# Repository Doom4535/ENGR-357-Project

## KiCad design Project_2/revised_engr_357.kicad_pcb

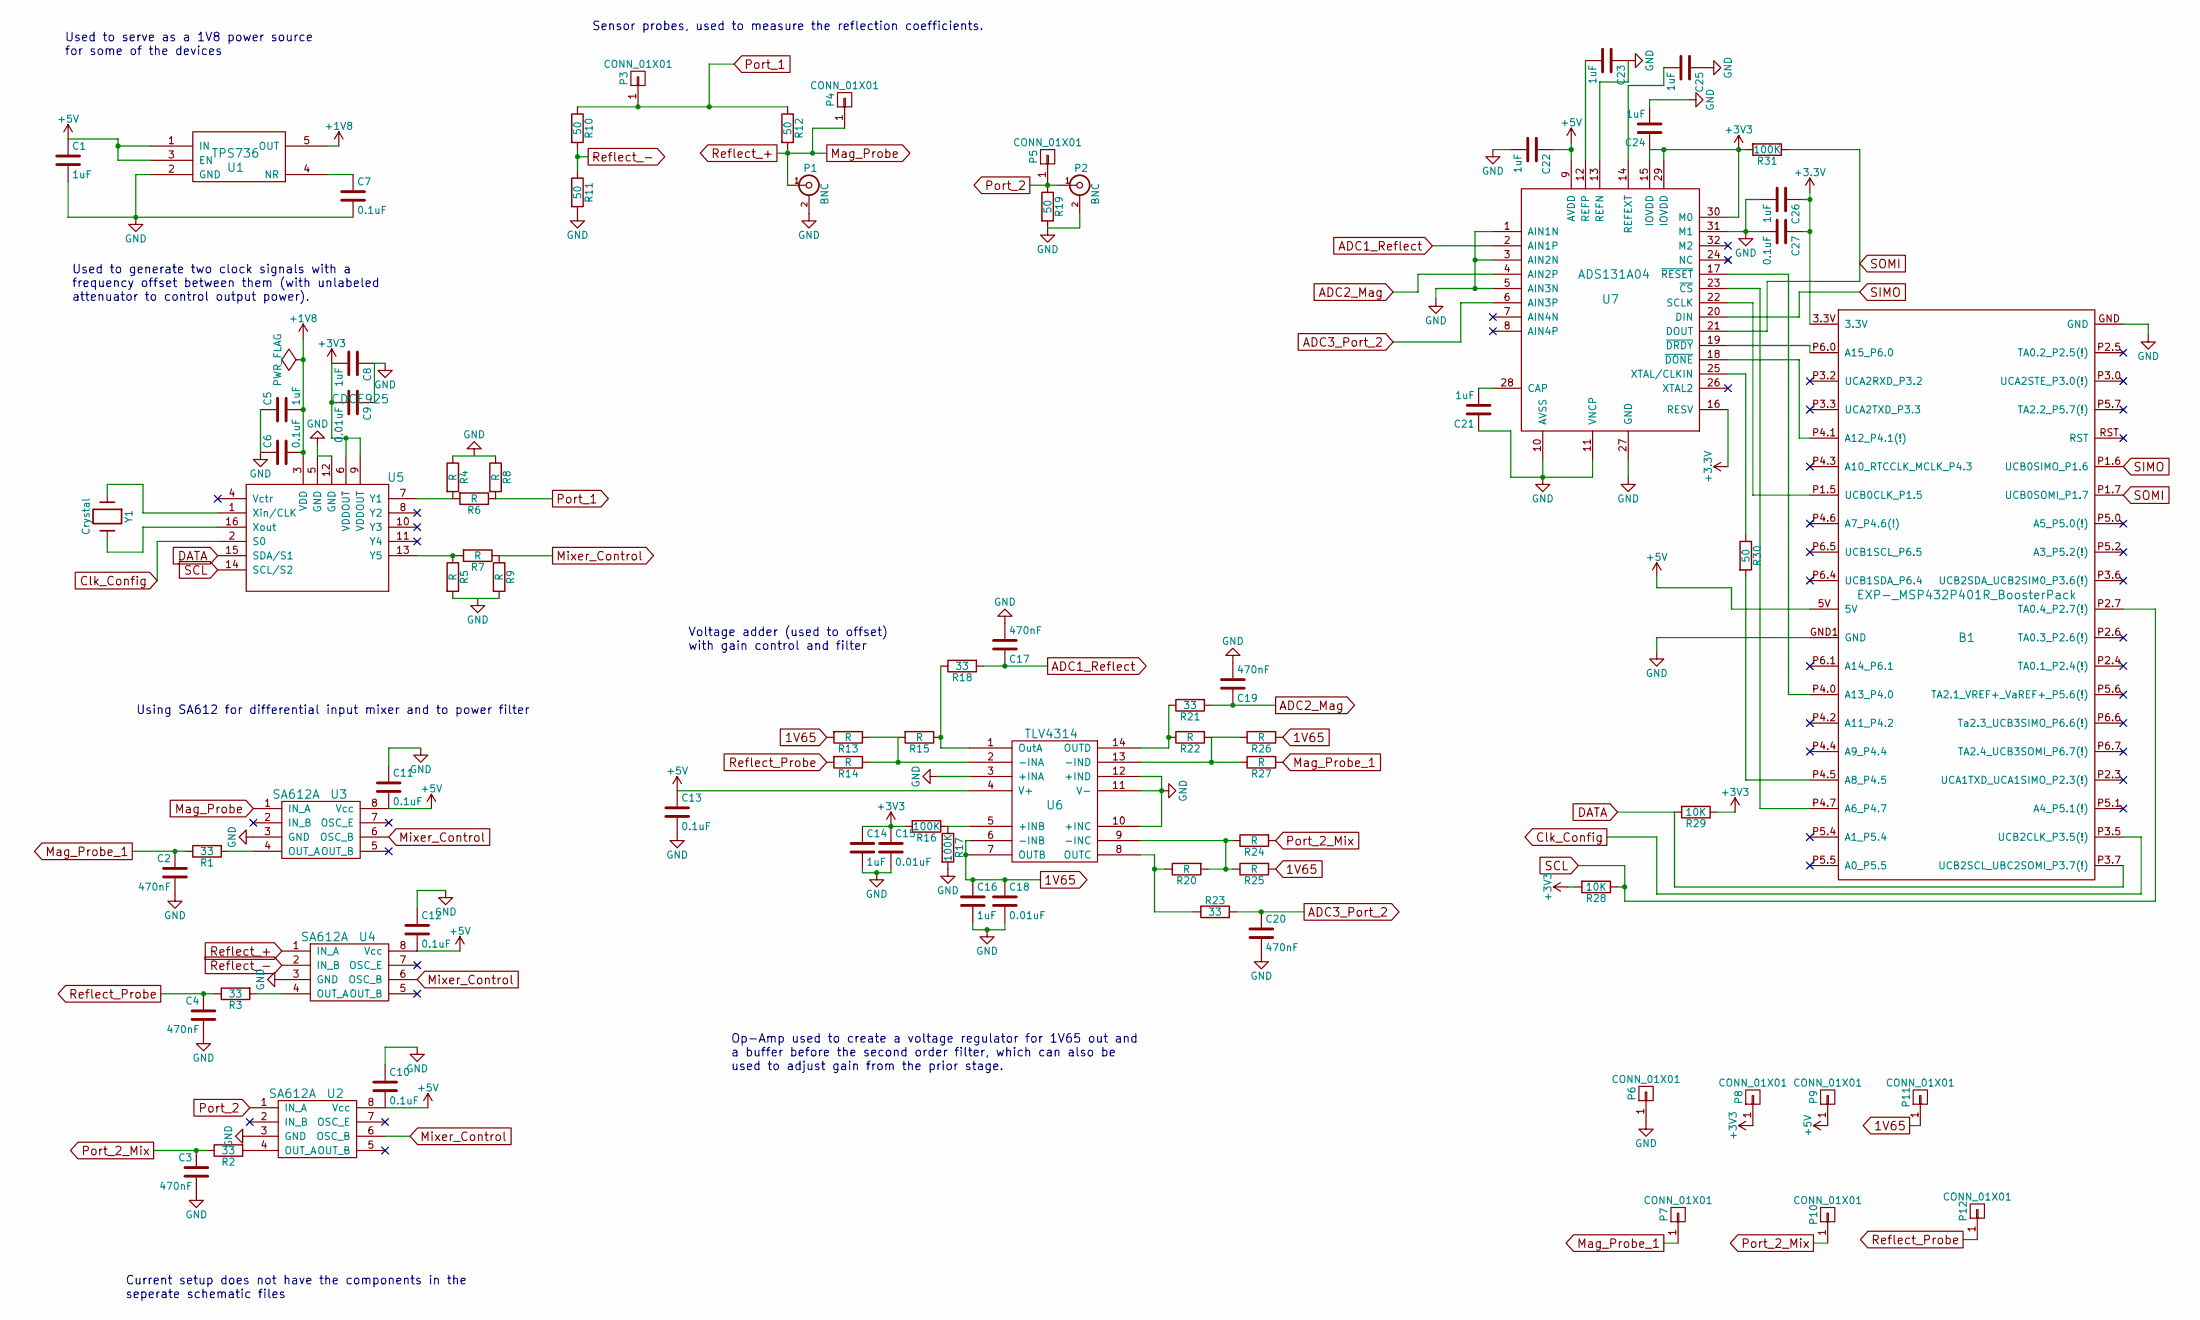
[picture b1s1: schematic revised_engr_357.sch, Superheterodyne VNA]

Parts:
B1: EXP-_MSP432P401R_BoosterPack; TI_BoosterPack
C1, C5, C8, C14, C16, C21, C22, C23, C24, C25, C26: 1uF; C_0805
C2, C3, C4, C17, C19, C20: 470nF; C_0805
C6, C7, C10, C11, C12, C13, C27: 0.1uF; C_0805
C9, C15, C18: 0.01uF; C_0805
P1, P2: BNC; BNC_Socket_TYCO-AMP
P3, P4, P5, P6, P7, P8, P9, P10, P11, P12: CONN_01X01; Measurement_Point_Round-SMD-Pad_Small
R1, R2, R3, R18, R21, R23: 33; R_0805
R4, R5, R6, R7, R8, R9, R13, R14, R15, R20, R22, R24, R25, R26, R27: R; R_0805
R10, R11, R12, R19, R30: 50; R_0805
R16, R17, R31: 100K; R_0805
R28, R29: 10K; R_0805
U1: TPS736; SOT-23-5
U2, U3, U4: SA612A; SO-8
U5: CDCE925; TSSOP-16_4.4x5mm_Pitch0.65mm
U6: TLV4314; TSSOP-14_4.4x5mm_Pitch0.65mm
U7: ADS131A04; LQFP-32_5x5mm_Pitch0.5mm
Y1: Crystal; Crystal_SMD_2520_4Pads

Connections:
1V65: C16.1, C18.1, P11.1, R13.2, R25.2, R26.2, U6.6 (-INB), U6.7 (OUTB)
+1V8: C5.2, C6.2, U1.5 (OUT), U5.3 (VDD)
+5V: B1.5V, C1.1, C10.2, C11.2, C12.2, C13.1, C22.1, P9.1, U1.1 (IN), U1.3 (EN), U2.8 (Vcc), U3.8 (Vcc), U4.8 (Vcc), U6.4 (V+), U7.9 (AVDD)
ADC1_Reflect: C17.1, R18.2, U7.2 (AIN1P)
ADC2_Mag: C19.1, R21.2, U7.4 (AIN2P)
ADC3_Port_2: C20.1, R23.2, U7.6 (AIN3P)
Clk_Config: B1.P3.5 (UCB2CLK_P3.5(!)), U5.2 (S0)
DATA: B1.P3.7 (UCB2SCL_UBC2SOMI_P3.7(!)), R29.2, U5.15 (SDA/S1)
Mag_Probe: P1.1 (In), P4.1, R12.2, U3.1 (IN_A), U4.1 (IN_A)
Mag_Probe_1: C2.1, P7.1, R1.1, R27.2
Mixer_Control: R7.1, R9.1, U2.6 (OSC_B), U3.6 (OSC_B), U4.6 (OSC_B)
unnamed: B1.P1.5 (UCB0CLK_P1.5), U7.22 (SCLK)
unnamed: B1.P4.0 (A13_P4.0), U7.17 (~RESET)
unnamed: B1.P4.1 (A12_P4.1(!)), U7.18 (~DONE)
unnamed: B1.P4.5 (A8_P4.5), R30.2
unnamed: B1.P4.7 (A6_P4.7), U7.23 (~CS)
unnamed: B1.P6.0 (A15_P6.0), U7.19 (~DRDY)
unnamed: C7.1, U1.4 (NR)
unnamed: C21.2, U7.28 (CAP)
unnamed: C23.2, U7.12 (REFP)
unnamed: C25.2, U7.14 (REFEXT)
unnamed: R1.2, U3.4 (OUT_A)
unnamed: R2.2, U2.4 (OUT_A)
unnamed: R3.2, U4.4 (OUT_A)
unnamed: R4.2, R6.2, U5.7 (Y1)
unnamed: R5.1, R7.2, U5.13 (Y5)
unnamed: R13.1, R14.1, R15.2, U6.2 (-INA)
unnamed: R15.1, R18.1, U6.1 (OutA)
unnamed: R16.1, R17.1, U6.5 (+INB)
unnamed: R20.1, R23.1, U6.8 (OUTC)
unnamed: R20.2, R24.1, R25.1, U6.9 (-INC)
unnamed: R21.1, R22.1, U6.14 (OUTD)
unnamed: R22.2, R26.1, R27.1, U6.13 (-IND)
unnamed: R30.1, U7.25 (XTAL/CLKIN)
unnamed: U5.1 (Xin/CLK), Y1.1
unnamed: U5.16 (Xout), Y1.2
Port_1: P3.1, R6.1, R8.2, R10.1, R12.1
Port_2: P2.1 (In), P5.1, R19.1, U2.1 (IN_A)
Port_2_Mix: C3.1, P10.1, R2.1, R24.2
Reflect_-: R10.2, R11.1, U4.2 (IN_B)
Reflect_Probe: C4.1, P12.1, R3.1, R14.2
SCL: B1.P2.7 (TA0.4_P2.7(!)), R28.1, U5.14 (SCL/S2)
SIMO: B1.P1.6 (UCB0SIMO_P1.6), U7.20 (DIN)
SOMI: B1.P1.7 (UCB0SOMI_P1.7), R31.1, U7.21 (DOUT)

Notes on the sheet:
Op-Amp used to create a voltage regulator for 1V65 out and a buffer before the second order filter, which can also be used to adjust gain from the prior stage.
Using SA612 for differential input mixer and to power filter
Used to generate two clock signals with a frequency offset between them (with unlabeled attenuator to control output power).
Used to serve as a 1V8 power source for some of the devices
Sensor probes, used to measure the reflection coefficients.
Current setup does not have the components in the seperate schematic files
Voltage adder (used to offset) with gain control and filter

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
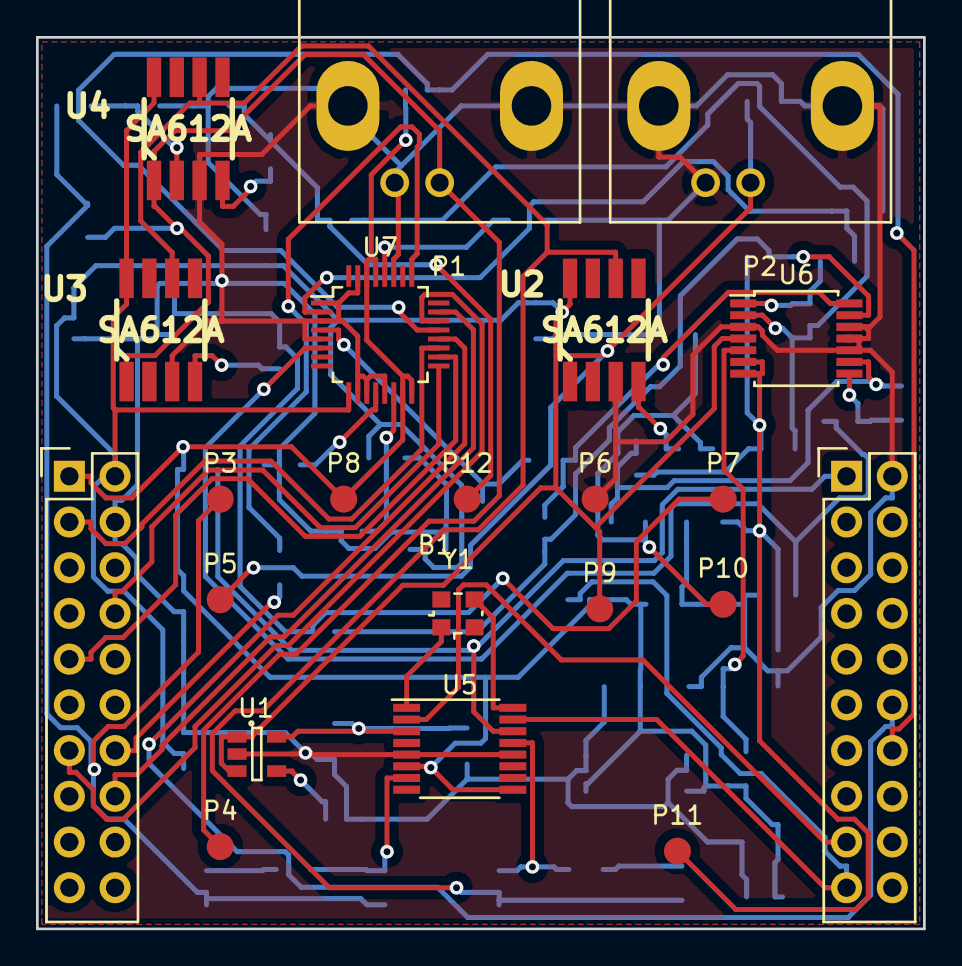
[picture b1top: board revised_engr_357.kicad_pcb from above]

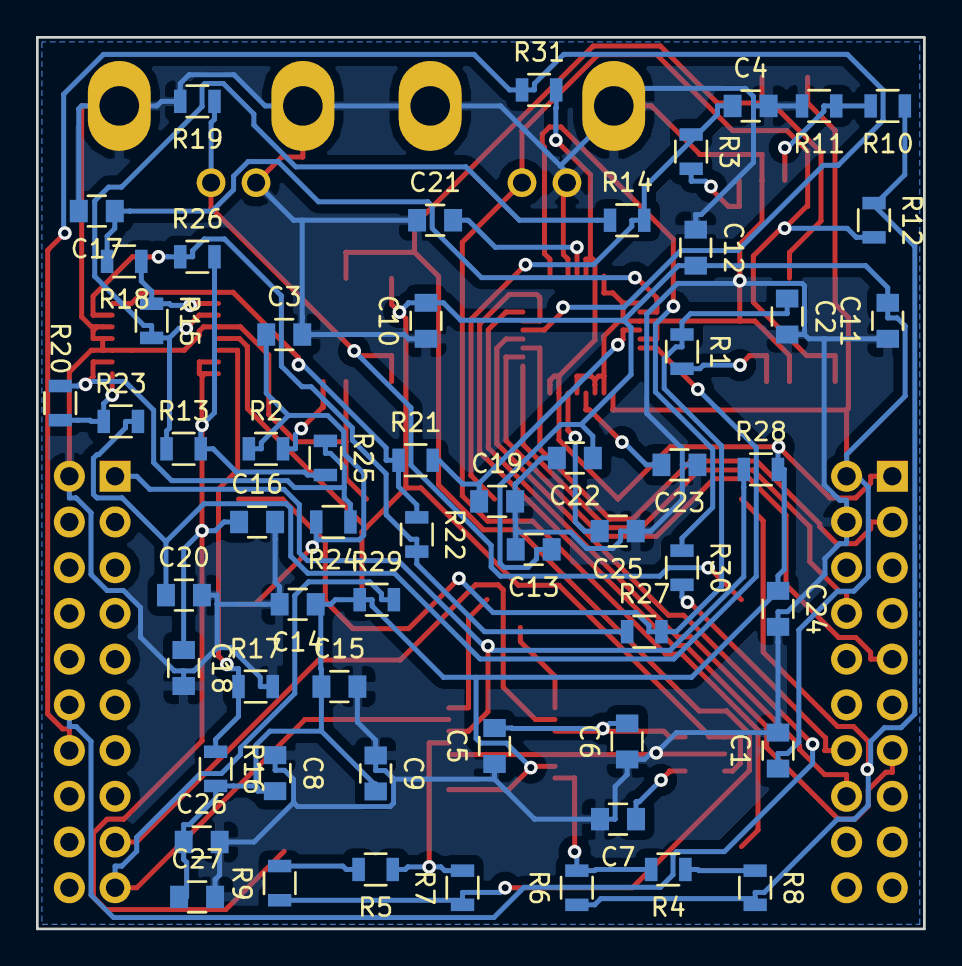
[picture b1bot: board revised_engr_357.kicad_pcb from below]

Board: 2 copper layers, 49.3 x 49.5 mm, 79 parts (58 on the bottom side), 48 nets.

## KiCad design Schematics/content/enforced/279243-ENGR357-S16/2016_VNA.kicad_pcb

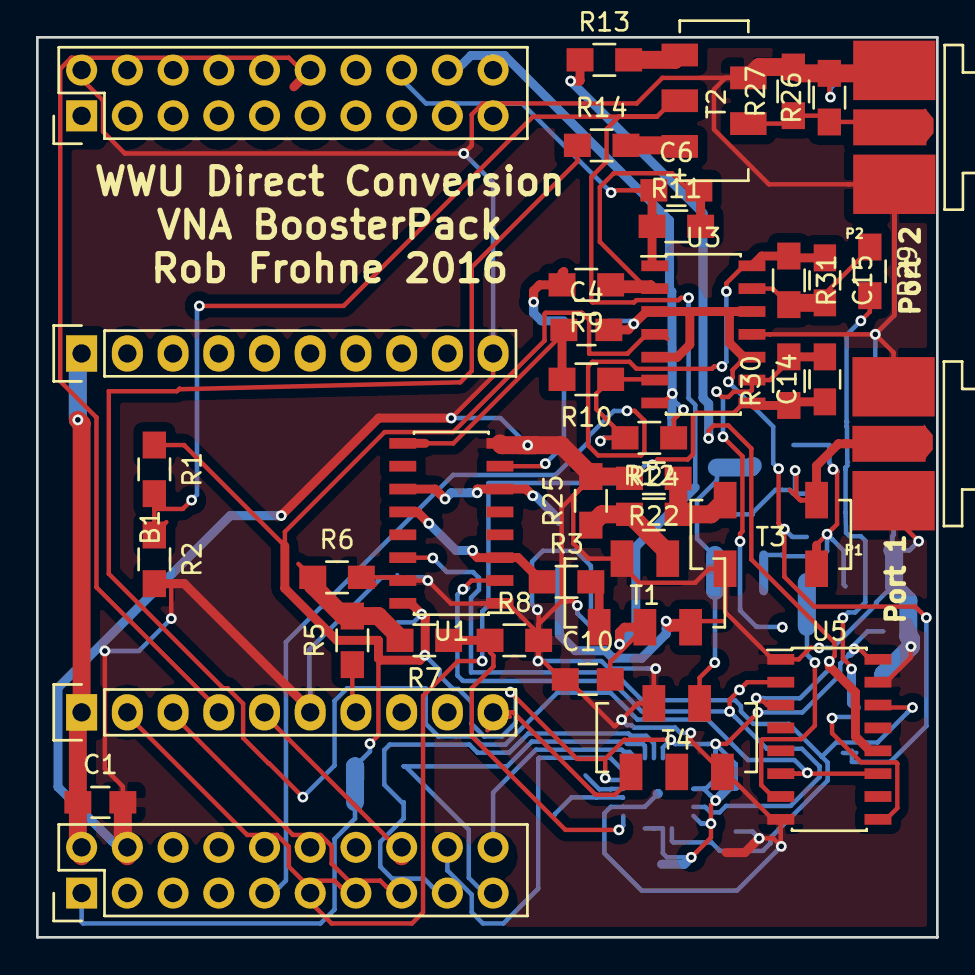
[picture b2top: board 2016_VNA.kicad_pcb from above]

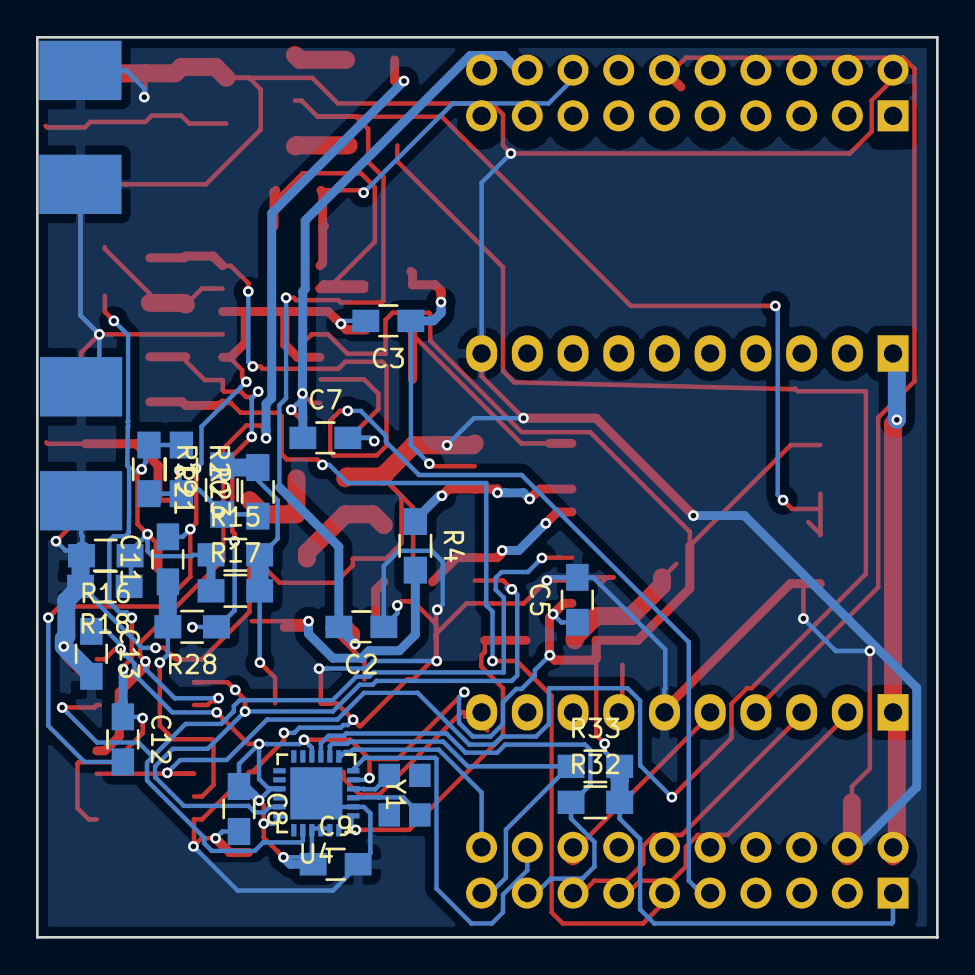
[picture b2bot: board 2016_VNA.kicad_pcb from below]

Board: 2 copper layers, 50.0 x 50.0 mm, 61 parts (23 on the bottom side), 47 nets.

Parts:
B1: EXP-_MSP432P401R_BoosterPack; TI_BoosterPack
C1, C2, C3, C4, C10, C11, C12: 0.1uF; C_0805_HandSoldering
C5, C13: 1.0uF; C_0805_HandSoldering
C6: 0.01 uF; C_0805_HandSoldering
C7, C14, C15: 0.01uF; C_0805_HandSoldering
C8, C9: 1.0 uF; C_0805_HandSoldering
P1, P2: BNC; SMA_EDGE
R1, R2: 2.2K; R_0805_HandSoldering
R3, R4, R13, R14: 1; R_0805_HandSoldering
R5, R7: 51; R_0805_HandSoldering
R6: 120; R_0805_HandSoldering
R8: 36; R_0805_HandSoldering
R9, R22, R24, R25, R28: R; R_0805_HandSoldering
R10, R29: 10; R_0805_HandSoldering
R11, R12, R30, R31: 4.7K; R_0805_HandSoldering
R15, R16, R17, R18, R19, R20, R21, R23, R26, R27: 100; R_0805_HandSoldering
R32, R33: 10K; R_0805_HandSoldering
T1, T2: 50:200 ohm; 4_to_1_Transmission_Line_Transformer
T3: Balun; 1_to_1_Balun
T4: 4:1 (Z); 4_to_1_Transmission_Line_Transformer
U1, U5: TS3A5017; SOIC-16_3.9x9.9mm_Pitch1.27mm
U2: HC-SR08_DDS_Module
U3: LMV324; SOIC-14_3.9x8.7mm_Pitch1.27mm
U4: 5P49V5923; NLG24_4x4mm_Pitch0.5mm
Y1: Xtal; JA4

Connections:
1.65: C3.2, C4.2, C11.2, C12.2, U3.3, U3.5, U3.10, U3.12
1.65V: C2.2, C10.2, R1.2, R2.1, T1.2, T2.2
4XF_I: U1.14, U4.20, U5.14
4XF_Q: U1.2, U4.17, U5.2
+3V3: B1.3.3V, C5.1, C8.1, C9.1, C13.1, R1.1, R32.2, R33.2, U1.16, U3.4, U4.5, U4.10, U4.15, U4.18, U4.21, U4.22, U4.23, U5.16
+5V: B1.5V, C1.1, U2.J2-1, U2.J4-1
CKSEL: B1.P5.4, U4.6
DDS_RST: B1.P4.7, U2.J4-5
FQ_UD: B1.P4.6, U2.J4-3
F_SINE: T4.3, U2.J410
GND: B1.GND, B1.GND1, C1.2, C2.1, C5.2, C8.2, C9.2, C10.1, C13.2, P1.2, P2.2, R2.2, R6.2, R8.2, R16.2, R18.2, R22.2, R25.2, R26.2, R27.2, T1.5, T2.5, T3.3, T4.1, T4.5, U1.1, U1.8, U1.15, U2.J4-6, U2.J210, U3.11, U4.2, U4.EPAD, U5.1, U5.8, U5.15
MO: B1.P1.6, U2.J4-4
unnamed: C3.1, R9.2, U1.7
unnamed: C4.1, R10.2, U1.9
unnamed: C6.2, R9.1, R11.2, U3.2
unnamed: C7.2, R10.1, R12.2, U3.6
unnamed: C11.1, R28.2, U5.7
unnamed: C12.1, R29.2, U5.9
unnamed: C14.2, R28.1, R30.2, U3.9
unnamed: C15.2, R29.1, R31.2, U3.13
unnamed: P1.1, R19.2, R20.2, R21.1, R23.1, T3.2
unnamed: R3.1, U1.3, U1.12
unnamed: R3.2, T1.3
unnamed: R4.1, U1.6, U1.11
unnamed: R4.2, T1.1
unnamed: R5.1, U2.J4-7
unnamed: R5.2, R6.1, R7.2
unnamed: R7.1, R8.1, U4.1
unnamed: R13.1, U5.3, U5.12
unnamed: R13.2, T2.3
unnamed: R14.1, U5.6, U5.11
unnamed: R14.2, T2.1
unnamed: R15.1, R16.1, R17.1, R18.1, R19.1, R20.1, T3.1
unnamed: R15.2, R17.2, R21.2, R23.2, T4.4
unnamed: R22.1, R24.2, T3.4
unnamed: U4.3, Y1.1
unnamed: U4.4, Y1.2
S11: R24.1, R25.1, T1.4
S11_I: B1.P5.0, C6.1, R11.1, U3.1
S11_Q: B1.P5.2, C7.1, R12.1, U3.7
S21: P2.1, R26.1, R27.1, T2.4
S21_I: B1.P4.3, C14.1, R30.1, U3.8
S21_Q: B1.P4.1, C15.1, R31.1, U3.14
SCL: B1.P6.5, R32.1, U4.9
SCLK: B1.P1.5, U2.J4-2
SD: B1.P5.5, U4.7
SDA: B1.P6.4, R33.1, U4.8

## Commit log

2016-04-19 Updating to fix broken diagrams
2016-04-19 Adding .gitignore
2016-04-20 Adding in additional library for the crystal that may be used and adding in some additional connections.
2016-04-20 Adding in some extra files and diagrams
2016-04-20 Adding in header pins for the MSP432 to a seperate library and moving some wiring
2016-04-20 Adding in simple voltage divider till a regulator can be decided on (preferably from TI), also added some power connections
2016-04-22 Adding in class libraries, extract the MSP432 library and change to using it instead of the current one
2016-04-22 Updated master by merging developement into it
2016-04-22 This closes #2 and adds a few wires
2016-04-25 Fixing flipped pins on the ADC
2016-04-25 added voltage regulator
2016-04-26 Updating, starting probes
2016-04-26 adding in bypass capacitors
2016-04-26 adding more component values
2016-04-26 saving before converting probes to work with reflection coefficient
2016-04-26 converted first probe to use reflection coefficient
2016-04-26 updated to use s-parameters (reflection coefficients) still uses only a first order low-pass filter (need to update to a second order)
2016-04-26 adding in export files
2016-04-27 Adding in two pullup resistors and the 3rd probe, also attached several datasheets
2016-04-28 probe fixed
2016-04-28 adding in export and renamed a flag
2016-04-28 Adding in second version of project with better organized schematic
2016-04-28 moving some folders around and performing minor housekeeping
2016-04-29 Finishing v2 of the schematic
2016-04-29 adding in pull up resistors
2016-04-29 adding in additional pdf
2016-04-29 added in resistor on clock source to ADC
2016-04-29 updating libraries to relative paths
2016-04-30 updating design, fixed low-pass filters, ect
2016-05-01 adding archive and pdf
2016-05-01 fixing voltage offset of transformer and adding in a 1V65 source
2016-05-02 adding in AVdd reference to the differential amps
2016-05-02 deleted random ground off page
2016-05-02 cleaning up schematic layout
2016-05-02 cleaning up some of the layouts and improved voltage regulator
2016-05-04 updating schematic to use new mixer
2016-05-04 adding in mixer library
2016-05-04 updating pdf
2016-05-04 finishing new mixers
2016-05-06 partial fix
2016-05-08 fixed probes, removed third order filter, fixed electrical rules checks
2016-05-08 working towards pcb
2016-05-08 working on adding footprints
2016-05-08 starting pcb layout
2016-05-08 fixed some errors and still working on pcb
2016-05-08 working on pcb layout
2016-05-08 testing different pcb layouts
2016-05-09 modifying files
2016-05-09 redoing pcb
2016-05-09 uploading pcb without ground plane
2016-05-09 finished preliminary schematic and pcb
2016-05-09 changning via size and adding test points
2016-05-09 adding in the ground pours that were forgotten in the previous commit
2016-05-09 adding in missing footprint library
2016-05-10 additional routing sizes
2016-05-10 larger via developement branch
2016-05-11 new enlarged via schematic
2016-06-07 commiting some past changes
2016-06-07 adding in test points
